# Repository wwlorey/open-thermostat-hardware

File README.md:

# open-thermostat-hardware
EE/CpE 4096/4097 Senior Design | Open Thermostat: a simple, smart thermostat

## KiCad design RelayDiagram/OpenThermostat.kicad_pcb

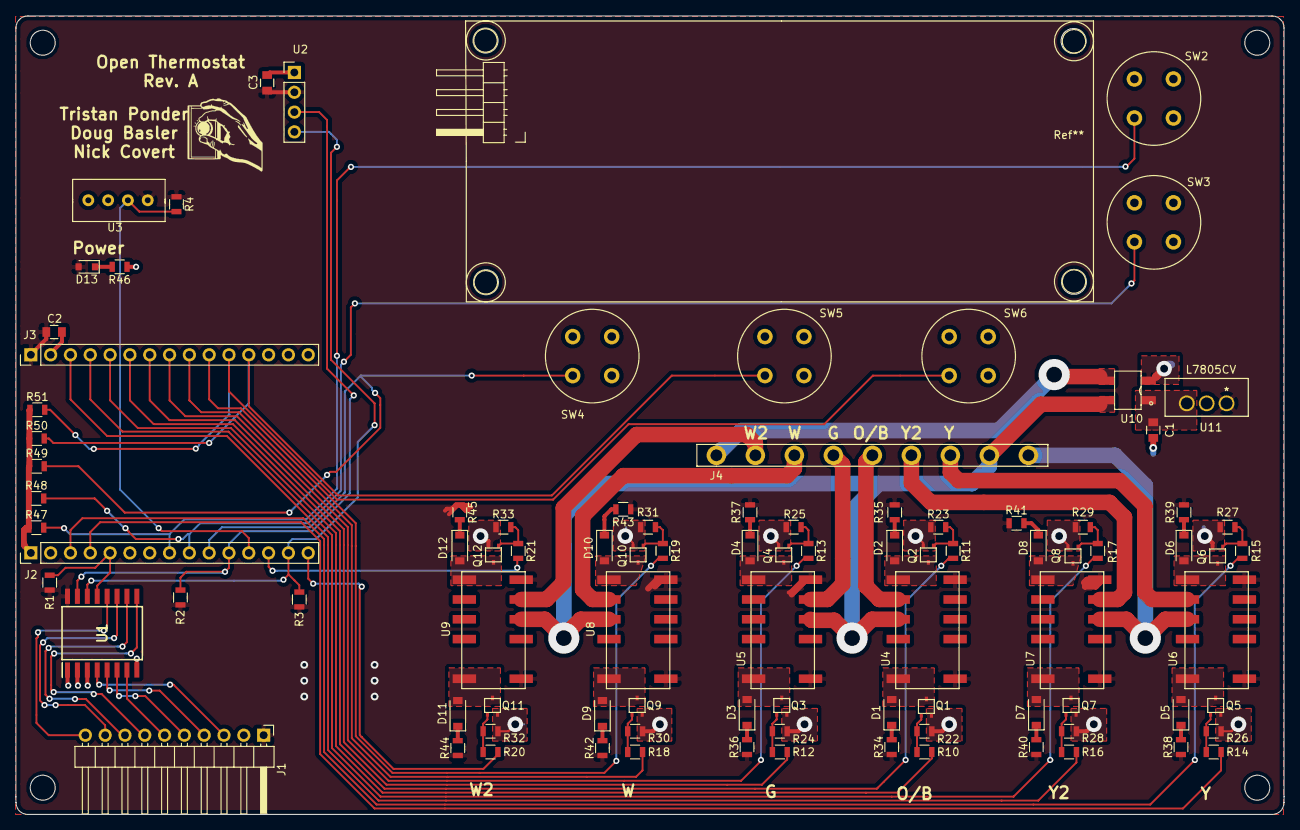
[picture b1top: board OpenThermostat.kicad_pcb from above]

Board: 2 copper layers, 162.6 x 102.4 mm, 95 parts (0 on the bottom side), 79 nets.

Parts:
C1, C2, C3: 10uF; Capacitor_0805
D1, D2, D3, D4, D5, D6, D7, D8, D9, D10, D11, D12: D; D_SOD-123
D13: LED; D_0805
J1: Conn_01x10_Female; Pin_Header_Angled_1x10_Pitch2.54mm
J2, J3: Conn_01x15_Female; Pin_Header_Straight_1x15_Pitch2.54mm
J4: Conn_01x09_Female; 5mmPtichBlockHeader
Q1, Q2, Q3, Q4, Q5, Q6, Q7, Q8, Q9, Q10, Q11, Q12: Q_NMOS_DGS; MCH3484-N-Channel-Mosfet
R1, R2, R3: 10k; R_0805
R4: 5k; R_0805
R10, R11, R12, R13, R14, R15, R16, R17, R18, R19, R20, R21, R34, R35, R36, R37, R38, R39, R40, R41, R42, R43, R44, R45, R46: 100; R_0805
R22, R23, R24, R25, R26, R27, R28, R29, R30, R31, R32, R33: 1M; R_0805
R47, R48, R49, R50, R51: 10K; R_0805
Ref**: Pin_Header_Angled_1x04_Pitch2.54mm; LCD
SW2, SW3, SW4, SW5, SW6: SW_Push; Pushbutton-KS-01Q-01
U1: PCF8574; SOIC127P1030X265-16N
U2: LCD; Pin_Header_Straight_1x04_Pitch2.54mm
U3: DHT11; DHT-11
U4, U5, U6, U7, U8, U9: EE2-3TNU-L_DPDT_Relay; EE2-5V-Relay
U10: MB10S-13; MB10F-13
U11: L7805CV

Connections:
+5V: C2.2, C3.2, D13.2, J1.1, J3.1, R1.2, R2.2, R3.1, R4.1, R34.1, R35.1, R36.1, R37.1, R38.1, R39.1, R40.1, R41.1, R42.1, R43.1, R44.1, R45.1, U1.16, U2.1, U3.1, U4.1, U4.6, U5.1, U5.6, U6.1, U6.6, U7.1, U7.6, U8.1, U8.6, U9.1, U9.6, U11.3
/R: J4.8, U4.4, U4.9, U5.4, U5.9, U8.4, U8.9, U9.4, U9.9, U10.2
/RC: J4.9, U6.4, U6.9, U7.4, U7.9
/V+: C1.1, U10.1, U11.1
GND: C1.2, C2.1, C3.1, J1.2, J2.2, J3.2, Q1.3, Q2.3, Q3.3, Q4.3, Q5.3, Q6.3, Q7.3, Q8.3, Q9.3, Q10.3, Q11.3, Q12.3, R22.2, R23.2, R24.2, R25.2, R26.2, R27.2, R28.2, R29.2, R30.2, R31.2, R32.2, R33.2, R46.1, SW2.2, SW3.2, SW4.2, SW5.2, SW6.2, U1.1, U1.2, U1.3, U1.8, U2.2, U3.4, U10.3, U11.2
unnamed: D1.1, R34.2
unnamed: D1.2, Q1.1, U4.12
unnamed: D2.1, R35.2
unnamed: D2.2, Q2.1, U4.7
unnamed: D3.1, R36.2
unnamed: D3.2, Q3.1, U5.12
unnamed: D4.1, R37.2
unnamed: D4.2, Q4.1, U5.7
unnamed: D5.1, R38.2
unnamed: D5.2, Q5.1, U6.12
unnamed: D6.1, R39.2
unnamed: D6.2, Q6.1, U6.7
unnamed: D7.1, R40.2
unnamed: D7.2, Q7.1, U7.12
unnamed: D8.1, R41.2
unnamed: D8.2, Q8.1, U7.7
unnamed: D9.1, R42.2
unnamed: D9.2, Q9.1, U8.12
unnamed: D10.1, R43.2
unnamed: D10.2, Q10.1, U8.7
unnamed: D11.1, R44.2
unnamed: D11.2, Q11.1, U9.12
unnamed: D12.1, R45.2
unnamed: D12.2, Q12.1, U9.7
unnamed: D13.1, R46.2
unnamed: J1.3, U1.4
unnamed: J1.4, U1.5
unnamed: J1.5, U1.6
unnamed: J1.6, U1.7
unnamed: J1.7, U1.9
unnamed: J1.8, U1.10
unnamed: J1.9, U1.11
unnamed: J1.10, U1.12
unnamed: J2.1, R47.1, R48.1, R49.1, R50.1, R51.1
unnamed: J2.3, R15.2
unnamed: J2.4, R14.2
unnamed: J2.5, R1.1, U1.13
unnamed: J2.8, R47.2, SW2.1
unnamed: J2.9, R48.2, SW3.1
unnamed: J2.10, R49.2, SW4.1
unnamed: J2.11, R2.1, U1.15, U2.4
unnamed: J2.12, R4.2, U3.2
unnamed: J2.13, R21.2
unnamed: J2.14, R3.2, U1.14, U2.3
unnamed: J2.15, R20.2
unnamed: J3.3, R16.2
unnamed: J3.4, R17.2
unnamed: J3.5, R10.2
unnamed: J3.6, R11.2
unnamed: J3.7, R12.2
unnamed: J3.8, R13.2
unnamed: J3.9, R18.2
unnamed: J3.10, R19.2
unnamed: J3.11, R51.2, SW6.1
unnamed: J3.12, R50.2, SW5.1
unnamed: J4.1, U10.4
unnamed: J4.2, U9.5, U9.8
unnamed: J4.3, U8.5, U8.8
unnamed: J4.4, U5.5, U5.8
unnamed: J4.5, U4.5, U4.8
unnamed: J4.6, U7.5, U7.8
unnamed: J4.7, U6.5, U6.8
unnamed: Q1.2, R10.1, R22.1
unnamed: Q2.2, R11.1, R23.1
unnamed: Q3.2, R12.1, R24.1
unnamed: Q4.2, R13.1, R25.1
unnamed: Q5.2, R14.1, R26.1
unnamed: Q6.2, R15.1, R27.1
unnamed: Q7.2, R16.1, R28.1
unnamed: Q8.2, R17.1, R29.1
unnamed: Q9.2, R18.1, R30.1
unnamed: Q10.2, R19.1, R31.1
unnamed: Q11.2, R20.1, R32.1
unnamed: Q12.2, R21.1, R33.1

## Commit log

2018-12-03 added lcd data sheet
2018-12-03 Move LCD data sheet to folder
2018-12-06 Real Data Sheet added
2018-12-08 Working on the M'F'in LCD boi
2019-01-17 more LCD stuff
2019-01-17 Relay and ESP32
2019-01-17 Changes to LCD Symbol
2019-01-18 Added LCD to full schematic, Changed LCD Symbol
2019-01-23 Some updates to the relay system for flyback and pulldown for FETs
2019-01-23 Add ESP32 datasheet
2019-01-24 added io for buttons and header for open pins, IO expander may not be needed because we have six open pins
2019-01-28 added io expander, may need different pin for scl
2019-01-28 Fixed My mistake overwriting the relay protection
2019-01-28 Comments
2019-01-30 Swapped out LCD and Rearranged pins to better implement I2C and the new relays
2019-01-31 Add relay lib part
2019-01-31 Double coil latching relays
2019-02-03 Relay input resistors
2019-02-03 Fixed flyback position. Might also add resistors w/ diode
2019-02-04 Resistors in serious with flyback diodes, resistor in series with buttons
2019-02-04 forgot about some resistors
2019-02-04 Messed up a relay output
2019-02-06 Made DHT-11 footprint, converted LCD, I/O expander, and micro to 5 volt power
2019-02-06 Hopefully added footprints for real
2019-02-06 assigned footprints to resistors(change coil resistors)
2019-02-10 Added footprints and started on PCB layout
2019-02-11 Started PCB design with I/O Expander and Temp sensor, changed wires for I2c
2019-02-11 Minor routing changes and placeholder LCD footprint added
2019-02-12 Added button footprints, PCB layout changes, changed schematic to fix relay coil polarity and also changed diode footprints.
2019-02-13 Created better LCD footprint(still needs double checking), flipped I/O Expander circuitry
2019-02-13 Routed LCD and placed buttons. Added edges to board, but it will most likely need to be extended to route the relays
2019-02-14 Added Power Components to schematic, Added Footprints
2019-02-14 Fixed broken schematic
2019-02-14 Moved buttons around, changed board size and grounded some components
2019-02-16 Change
2019-02-16 PCB updates
2019-02-16 relay pcb changes
2019-02-16 Relay updates
2019-02-20 Add license
2019-02-21 Major routing. Board should be nearly complete apart from review and minor changes.
2019-02-21 Fixed some relays not connected to +5V
2019-02-23 Moved 4 pin header for LCD
2019-02-23 MEETING CHANGES
2019-02-25 added mounting holes and power indicator LED
2019-02-25 Changed to big boy header and added great logo
2019-02-25 Created Rev A Gerber and Drill files
2019-03-20 changed ports on micro controller to get input only ports connected to switches
2019-04-29 Added pull up resistors
2019-05-01 Fixed relay R & RC connections, removed 1M ohm series button resistors, added 5V and GND to I/O header
2019-05-08 a list
